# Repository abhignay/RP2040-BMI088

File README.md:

# RP2040+BMI088

An RP2040 and BMI088 development board

Libraries - [KiCAD Source](https://github.com/abhignay/KiCAD-Libs)

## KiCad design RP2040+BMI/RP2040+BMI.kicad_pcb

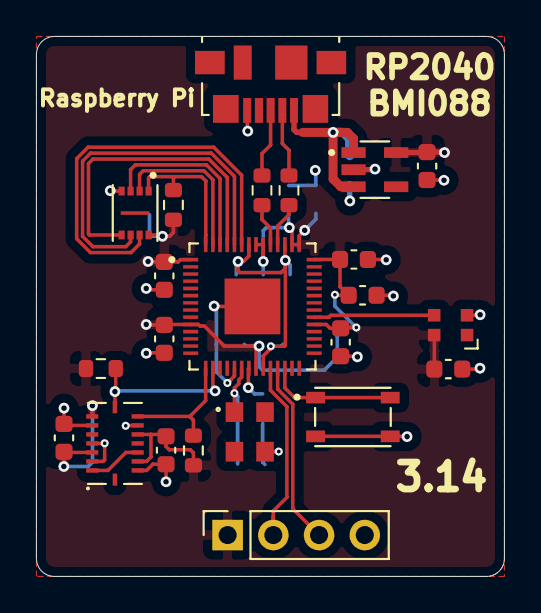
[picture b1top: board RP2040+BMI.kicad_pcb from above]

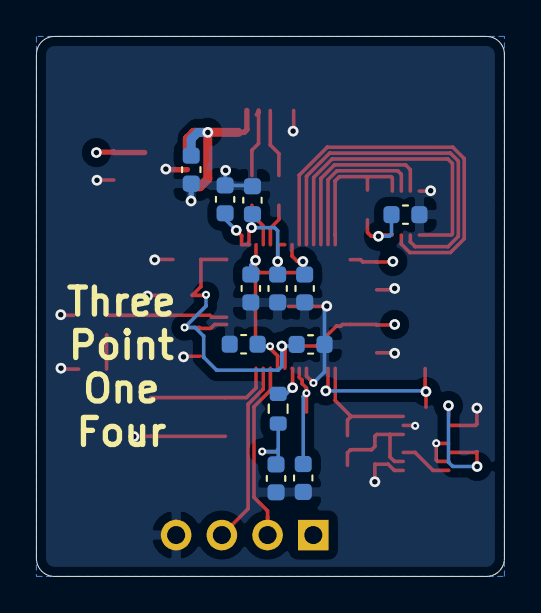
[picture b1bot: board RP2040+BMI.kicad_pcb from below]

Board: 2 copper layers, 26.0 x 30.0 mm, 35 parts (12 on the bottom side), 24 nets.

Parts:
C1, C2, C7, C10, C11, C13, C14, C15, C16, C17, C18, C19, C20: 0.1uF; C_0603_1608Metric
C3, C4, C8, C9: 1uF; C_0603_1608Metric
C5, C6: 27pF; C_0603_1608Metric
C12: 10uF; C_0603_1608Metric
D1: NeoPixel; WS2812B-2020_2x2mm
J1: USB_B_Micro; Micro_USB
J2: Conn_01x04_Male; PinSocket_1x04_P2.54mm_Vertical
R1: 10k; R_0603_1608Metric
R2: 1k; R_0603_1608Metric
R3, R4: 27ohm; R_0603_1608Metric
R5, R6: 4.7k; R_0603_1608Metric
SW1: SW_Push_Dual; SW_PTS810_SJM_250_SMTR_LFS
U1: RP2040
U2: W25Q16JVUXIQ
U3: AP7343-33W5-7
U4: BMI088; BMI088_usethisboi_QFN_Package
U5: 4Pin-Crystal; 16mhZ_Crystal

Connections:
+1V1: C8.1, C15.1, C18.1, U1.23, U1.45, U1.50
+3V3: C1.1, C2.1, C4.1, C7.1, C9.1, C10.1, C11.1, C12.1, C13.1, C14.1, C16.1, C17.1, C19.1, C20.1, D1.4, J2.1, R1.2, R5.2, R6.2, U1.1, U1.10, U1.22, U1.33, U1.42, U1.43, U1.44, U1.48, U1.49, U2.8, U3.5, U4.3, U4.7, U4.11, U4.14
+5V: C3.1, J1.1, U3.1, U3.3
/CS: R1.1, U1.56, U2.1
/D+: J1.3, R3.1
/D-: J1.2, R4.1
/LED: D1.3, U1.34
/QSPI_IO0: U1.53, U2.5
/QSPI_IO1: U1.55, U2.2
/QSPI_IO2: U1.54, U2.3
/QSPI_IO3: U1.51, U2.7
/RST: SW1.1, SW1.2, U1.26
/SCK: U1.52, U2.6
/SCL: R5.1, U1.16, U4.8
/SDA: R6.1, U1.15, U4.9
/SWCLK: J2.2, U1.24
/SWD: J2.3, U1.25
GND: C1.2, C2.2, C3.2, C4.2, C5.2, C6.1, C7.2, C8.2, C9.2, C10.2, C11.2, C12.2, C13.2, C14.2, C15.2, C16.2, C17.2, C18.2, C19.2, C20.2, D1.2, J1.5, J2.4, SW1.3, SW1.4, U1.19, U1.57, U2.4, U3.2, U4.2, U4.4, U4.6, U4.10, U4.15
unnamed: C5.1, U1.20, U5.1
unnamed: C6.2, R2.1, U5.3
unnamed: R2.2, U1.21
unnamed: R3.2, U1.47
unnamed: R4.2, U1.46
unnamed: U4.1, U4.13
